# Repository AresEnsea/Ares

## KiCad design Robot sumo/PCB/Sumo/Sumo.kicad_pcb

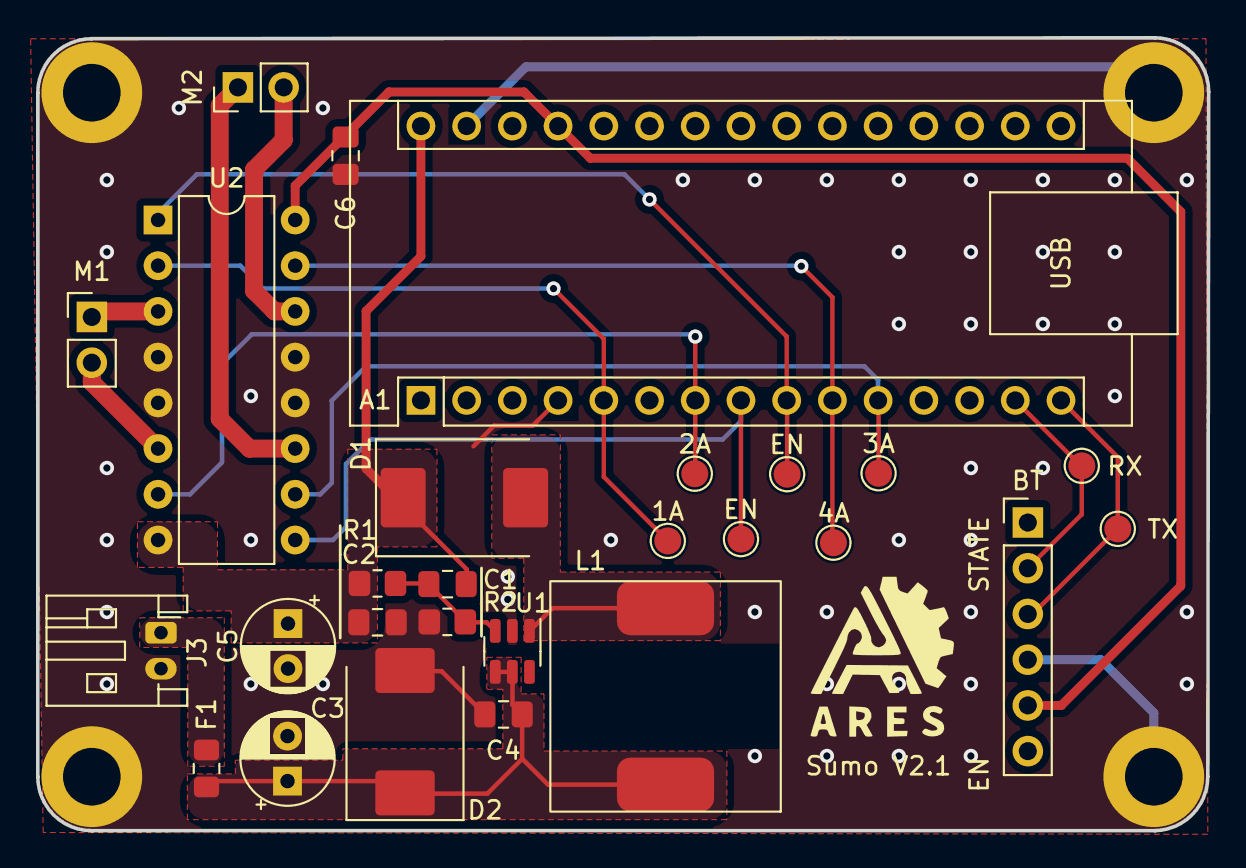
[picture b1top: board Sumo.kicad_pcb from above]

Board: 2 copper layers, 65.1 x 44.0 mm, 32 parts (0 on the bottom side), 19 nets.

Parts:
1A, 2A, 3A, 4A: TestPoint; TestPoint_Pad_D1.5mm
A1: Arduino_Nano_v2.x; Arduino_Nano
BT: BT; PinHeader_1x06_P2.54mm_Vertical
C1: 47p; C_0805_2012Metric_Pad1.18x1.45mm_HandSolder
C2, C4: 22u; C_0805_2012Metric_Pad1.18x1.45mm_HandSolder
C3, C5: 100u; CP_Radial_D5.0mm_P2.50mm
C6: 1u; C_0805_2012Metric_Pad1.18x1.45mm_HandSolder
D1, D2: D_Schottky; D_SMC
EN: TestPoint; TestPoint_Pad_D1.5mm
EN#2: TestPoint; TestPoint_Pad_D1.5mm
F1: 5A; Fuse_0805_2012Metric_Pad1.15x1.40mm_HandSolder
J1, J2, J4, J5: Screw_Terminal_01x01; MountingHole_3.2mm_M3_DIN965_Pad
J3: Bat; JST_PH_S2B-PH-K_1x02_P2.00mm_Horizontal
L1: 10u; WE-PDA
M1: M1; PinHeader_1x02_P2.54mm_Vertical
M2: M2; PinHeader_1x02_P2.54mm_Vertical
R1: 100k; R_0805_2012Metric_Pad1.20x1.40mm_HandSolder
R2: 5,6k; R_0805_2012Metric_Pad1.20x1.40mm_HandSolder
RX: TestPoint; TestPoint_Pad_D1.5mm
Sumo V2.1: LOGO; ares_logo
TX: TestPoint; TestPoint_Pad_D1.5mm
U1: MT3608; SOT-23-6
U2: L293D; DIP-16_W7.62mm

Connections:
1A: 1A.1, A1.5 (D2), U2.2 (1A)
2A: 2A.1, A1.7 (D4), U2.7 (2A)
3A: 3A.1, A1.11 (D8), U2.10 (3A)
4A: 4A.1, A1.10 (D7), U2.15 (4A)
+5V: A1.27 (+5V), BT.5, C6.1, U2.16 (VCC1)
+12V: A1.30 (VIN), C1.1, C2.1, C5.1, D1.1 (K), R1.1, U2.8 (VCC2)
+BATT: F1.1, J3.1
EN12: A1.9 (D6), EN#2.1, U2.1 (EN1,2)
EN34: A1.8 (D5), EN.1, U2.9 (EN3,4)
GND: A1.4 (GND), A1.29 (GND), BT.4, C2.2, C3.2, C4.2, C5.2, C6.2, D2.2 (A), J1.1, J2.1, J3.2, J4.1, J5.1, R2.2, U1.2 (GND), U2.4 (GND), U2.5 (GND), U2.12 (GND), U2.13 (GND)
unnamed: D1.2 (A), L1.2, U1.1 (SW)
unnamed: C3.1, C4.1, D2.1 (K), F1.2, L1.1, U1.4 (EN), U1.5 (IN)
unnamed: M1.1, U2.3 (1Y)
unnamed: M1.2, U2.6 (2Y)
unnamed: M2.1, U2.11 (3Y)
unnamed: M2.2, U2.14 (4Y)
unnamed: C1.2, R1.2, R2.1, U1.3 (FB)
RX: A1.14 (D11), BT.2, RX.1
TX: A1.15 (D12), BT.3, TX.1

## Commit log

2022-10-07 majcodesumo
2022-10-20 AX12Add
2022-10-26 AXandF303
2022-10-29 V6sumo
2022-11-06 sumobotOk
2022-11-09 sumobotBackwardVer
2022-11-22 ecran
2022-11-24 faire fonctionner les ecrans sans touch
    voir https://github.com/afiskon/stm32-ili9341
2023-01-26 join
2023-01-26 newSumoRoobot
2023-02-02 V8Lipo
2023-08-28 Ajout du dossier Activité de rentrée 2023
2023-08-28 Corrections mineures
2023-11-18 Ajout des activités de rentrée
2023-11-18 Ajout du dossier Borne d'arcade
2023-11-23 added Sumo V2 project
2023-11-23 Added BOM
2024-01-18 ajout des models 3D du sumoBot
